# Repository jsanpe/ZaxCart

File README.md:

# ZaxCart
A kicad implementation of a C64 cartridge with potential to be used as a Super Zaxxon compatible cart

## Description
This Kicad project implements a C64 cartridge with an EEPROM socket and some external logic that can be use from the C64. A similar concept was used for the Super Zaxxon cartridge, which theoretically this cart could support. Its main purpose is to be able to test PLA and other ICs from the C64 by running particularly demanding code to stress the whole system.

This PCB is directly derived from the [OpenC64Cart](https://github.com/SukkoPera/OpenC64Cart) by SukkoPera, so all the credit for him for most of the footprints used.

## Manufacturing the PCB

This is a pretty straightforward 2-layer PCB with few components. The gerbers attached can be directly used to get the PCB manufactured for you. It is important for the health of the C64 to ask for bevelled edges with Immersion (ENIG) or Hard Gold contacts. These extra features will cost you some extra cash, but will save you issues with your machines in the long run.

## Soldering Components

The PCB has been designed to use SMD capacitors. I went for 0805s as this size is pretty manageable and allows for using 0603s (which is my main inventory) without issue. The capacitors are located below the sockets for the ICs, so remember to solder them first :)

## Firmware

This project does not include any particular firmware. Depending on your target use, you may find this page about [replicating the Super Zaxxon cart](https://www.hackup.net/2018/10/super-zaxxon-replica/) useful. You can of course code your own C64 applications. In any case, a good EEPROM programmer and a batch of 27512 memories will come extra handy. Remember to buy the eletrically erasable parts, they are dirt cheap and really convenient. 

Note: I will not be responding any issues or questions regarding firmware/software to be used with this cart. 

## BOM

|Value	|Designator|	Footprint|
|-------|----------|-----------|
|100nF	|C1, C2,C3	|Capacitor_SMD:C_0805|
|27512	|U2	|DIP-28_W15.24mm_Socket|
|74LS74	|U3	|DIP-14_W7.62mm_Socket|
|74LS00	|U4	|DIP-14_W7.62mm_Socket|

## License
This project is licensed under the terms of the MIT License. The original OpenC64Cart project does not currently name any licenses, so this could change in the future if an imcompatibility between licenses is identified. However, the current limitations of liability and warranty will always hold.

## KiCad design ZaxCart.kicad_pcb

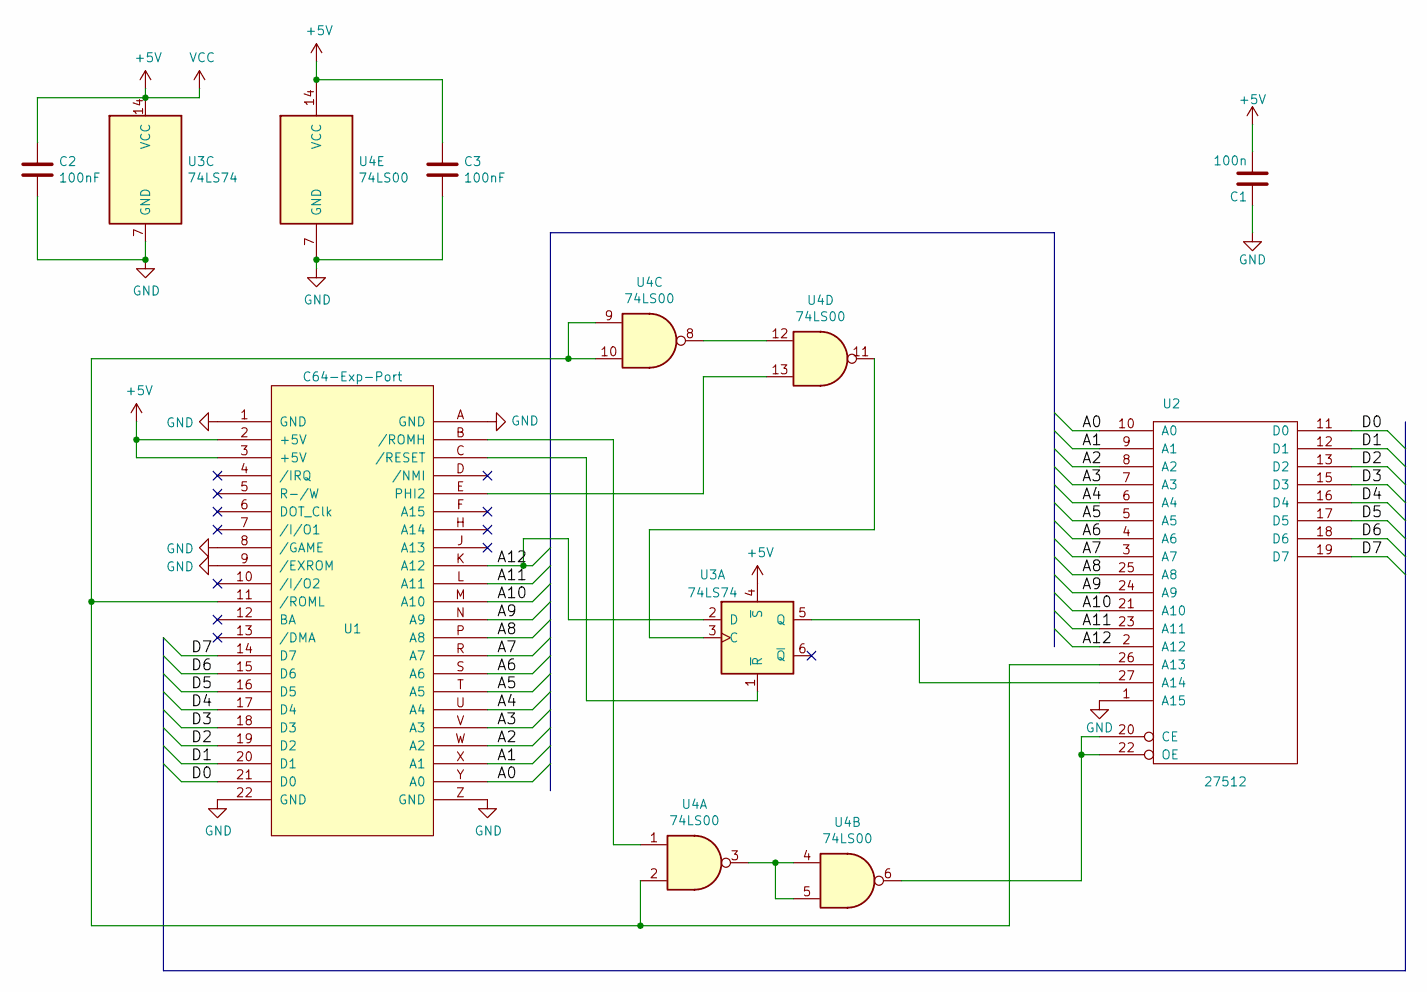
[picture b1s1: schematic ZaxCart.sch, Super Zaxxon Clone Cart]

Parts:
C1: 100n; C_0805_2012Metric_Pad1.18x1.45mm_HandSolder
C2, C3: 100nF; C_0805_2012Metric_Pad1.18x1.45mm_HandSolder
U1: C64-Exp-Port; C64-Cart
U2: 27512; DIP-28_W15.24mm_Socket
U3: 74LS74; DIP-14_W7.62mm_Socket
U4: 74LS00; DIP-14_W7.62mm_Socket

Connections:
+5V: C1.2, C2.1, C3.1, U1.2 (+5V), U1.3 (+5V), U2.28 (VCC), U3.4 (~S), U3.14 (VCC), U4.14 (VCC)
/A0: U1.Y (A0), U2.10 (A0)
/A1: U1.X (A1), U2.9 (A1)
/A2: U1.W (A2), U2.8 (A2)
/A3: U1.V (A3), U2.7 (A3)
/A4: U1.U (A4), U2.6 (A4)
/A5: U1.T (A5), U2.5 (A5)
/A6: U1.S (A6), U2.4 (A6)
/A7: U1.R (A7), U2.3 (A7)
/A8: U1.P (A8), U2.25 (A8)
/A9: U1.N (A9), U2.24 (A9)
/A10: U1.M (A10), U2.21 (A10)
/A11: U1.L (A11), U2.23 (A11)
/A12: U1.K (A12), U2.2 (A12), U3.2 (D)
/D0: U1.21 (D0), U2.11 (D0)
/D1: U1.20 (D1), U2.12 (D1)
/D2: U1.19 (D2), U2.13 (D2)
/D3: U1.18 (D3), U2.15 (D3)
/D4: U1.17 (D4), U2.16 (D4)
/D5: U1.16 (D5), U2.17 (D5)
/D6: U1.15 (D6), U2.18 (D6)
/D7: U1.14 (D7), U2.19 (D7)
GND: C1.1, C2.2, C3.2, U1.1 (GND), U1.8 (/GAME), U1.9 (/EXROM), U1.22 (GND), U1.A (GND), U1.Z (GND), U2.1 (A15), U2.14 (GND), U3.7 (GND), U4.7 (GND)
unnamed: U1.11 (/ROML), U2.26 (A13), U4.2, U4.9, U4.10
unnamed: U1.B (/ROMH), U4.1
unnamed: U1.C (/RESET), U3.1 (~R)
unnamed: U1.E (PHI2), U4.13
unnamed: U2.20 (CE), U2.22 (OE), U4.6
unnamed: U2.27 (A14), U3.5 (Q)
unnamed: U3.3 (C), U4.11
unnamed: U4.3, U4.4, U4.5
unnamed: U4.8, U4.12

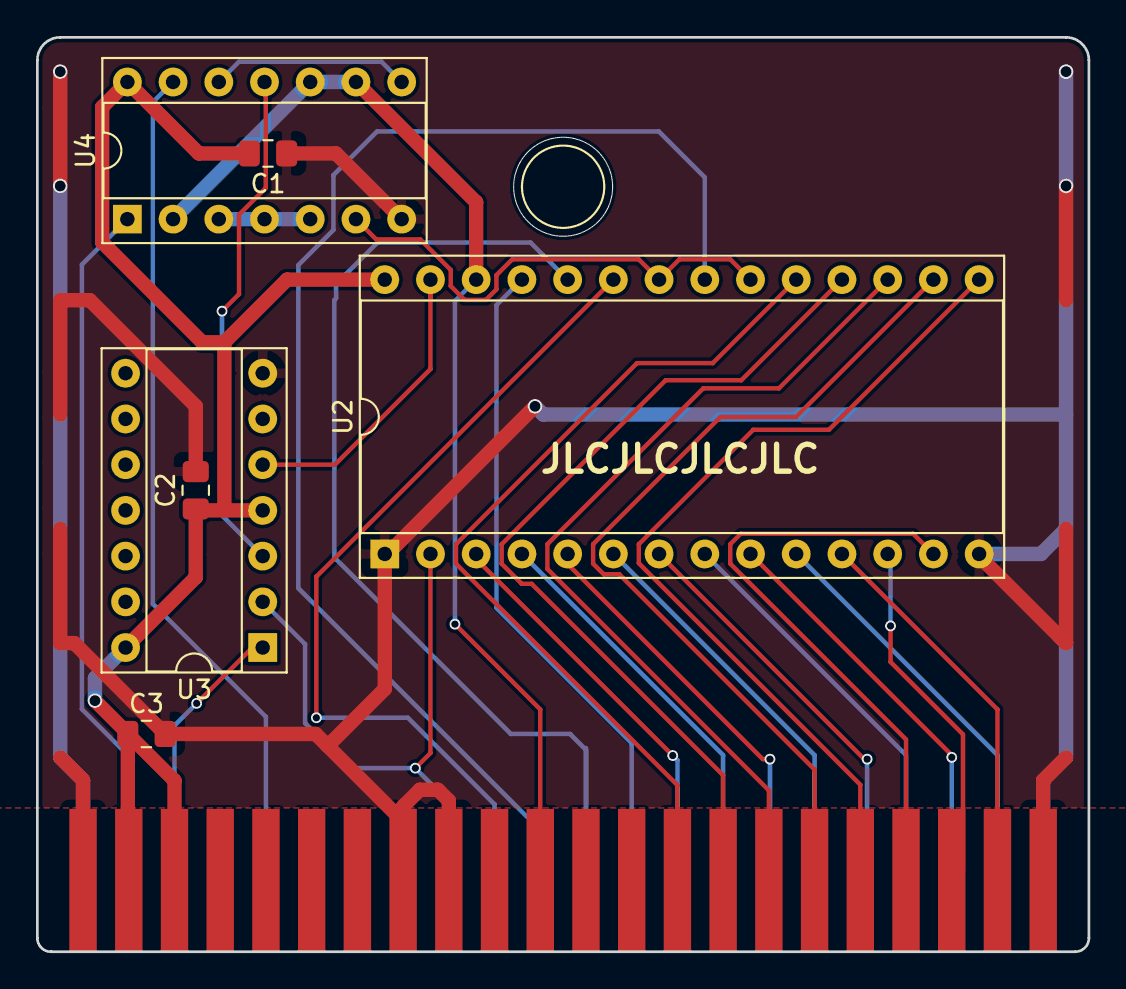
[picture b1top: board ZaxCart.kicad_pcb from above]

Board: 2 copper layers, 58.4 x 50.8 mm, 8 parts (0 on the bottom side), 32 nets.

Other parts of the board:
J99: PEG_HOLE; 1pin

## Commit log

2021-08-25 Initial Release
2021-08-25 Add image to readme
2021-08-25 Reduce image size
